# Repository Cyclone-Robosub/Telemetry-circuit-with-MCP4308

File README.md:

# Telemetry-circuit-with-MCP4308
This is the telemetry circuit that Marco Chen made during winter and spring quarter.

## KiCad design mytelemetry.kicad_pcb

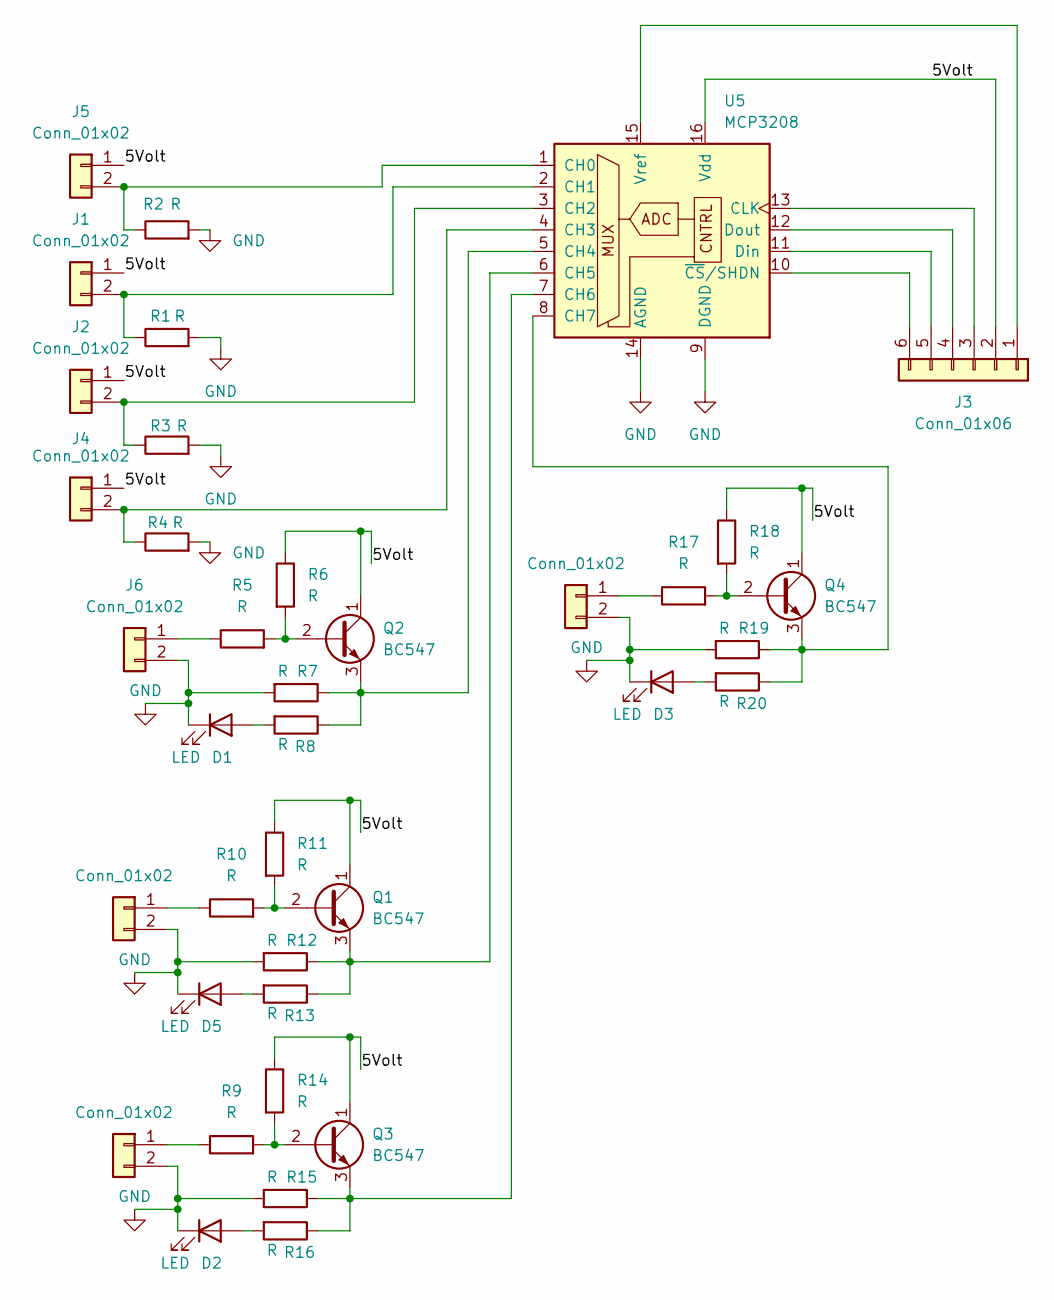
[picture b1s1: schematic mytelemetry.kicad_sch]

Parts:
D1, D2, D3, D5: LED; LED_APT2012LZGCK
J1, J2, J4, J5, J6, J7, J8, J9: Conn_01x02; JST_PH_B2B-PH-K_1x02_P2.00mm_Vertical
J3: Conn_01x06; JST_PH_B6B-PH-K_1x06_P2.00mm_Vertical
Q1, Q2, Q3, Q4: BC547; TO-92_Inline
R1, R2, R3, R4, R5, R6, R7, R8, R9, R10, R11, R12, R13, R14, R15, R16, R17, R18, R19, R20: R; R_0805_2012Metric_Pad1.20x1.40mm_HandSolder
U5: MCP3208; DIP-18_W7.62mm_SMDSocket_SmallPads

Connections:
/5Volt: J1.1, J2.1, J3.2, J4.1, J5.1, Q1.1 (C), Q2.1 (C), Q3.1 (C), Q4.1 (C), R6.1, R11.1, R14.1, R18.1, U5.16 (Vdd); also elsewhere on the board
GND: D1.1 (K), D2.1 (K), D3.1 (K), D5.1 (K), J6.2, J7.2, J8.2, J9.2, R1.2, R2.2, R3.2, R4.2, R7.2, R12.2, R15.2, R19.2, U5.9 (DGND), U5.14 (AGND); also elsewhere on the board
unnamed: D1.2 (A), R8.2
unnamed: D2.2 (A), R16.2
unnamed: D3.2 (A), R20.2
unnamed: D5.2 (A), R13.2
unnamed 6: J1.2, R1.1, U5.2 (CH1); also elsewhere on the board
unnamed 7: J2.2, R3.1, U5.3 (CH2); also elsewhere on the board
unnamed 8: J3.1, U5.15 (Vref); also elsewhere on the board
unnamed 9: J3.3, U5.13 (CLK); also elsewhere on the board
unnamed 10: J3.4, U5.12 (Dout); also elsewhere on the board
unnamed 11: J3.5, U5.11 (Din); also elsewhere on the board
unnamed 12: J3.6, U5.10 (~CS/SHDN); also elsewhere on the board
unnamed 13: J4.2, R4.1, U5.4 (CH3); also elsewhere on the board
unnamed 14: J5.2, R2.1, U5.1 (CH0); also elsewhere on the board
unnamed: J6.1, R5.1
unnamed: J7.1, R10.1
unnamed: J8.1, R9.1
unnamed: J9.1, R17.1
unnamed: Q1.2 (B), R10.2, R11.2
unnamed 20: Q1.3 (E), R12.1, R13.1, U5.6 (CH5); also elsewhere on the board
unnamed: Q2.2 (B), R5.2, R6.2
unnamed 22: Q2.3 (E), R7.1, R8.1, U5.5 (CH4); also elsewhere on the board
unnamed: Q3.2 (B), R9.2, R14.2
unnamed 24: Q3.3 (E), R15.1, R16.1, U5.7 (CH6); also elsewhere on the board
unnamed: Q4.2 (B), R17.2, R18.2
unnamed 26: Q4.3 (E), R19.1, R20.1, U5.8 (CH7); also elsewhere on the board

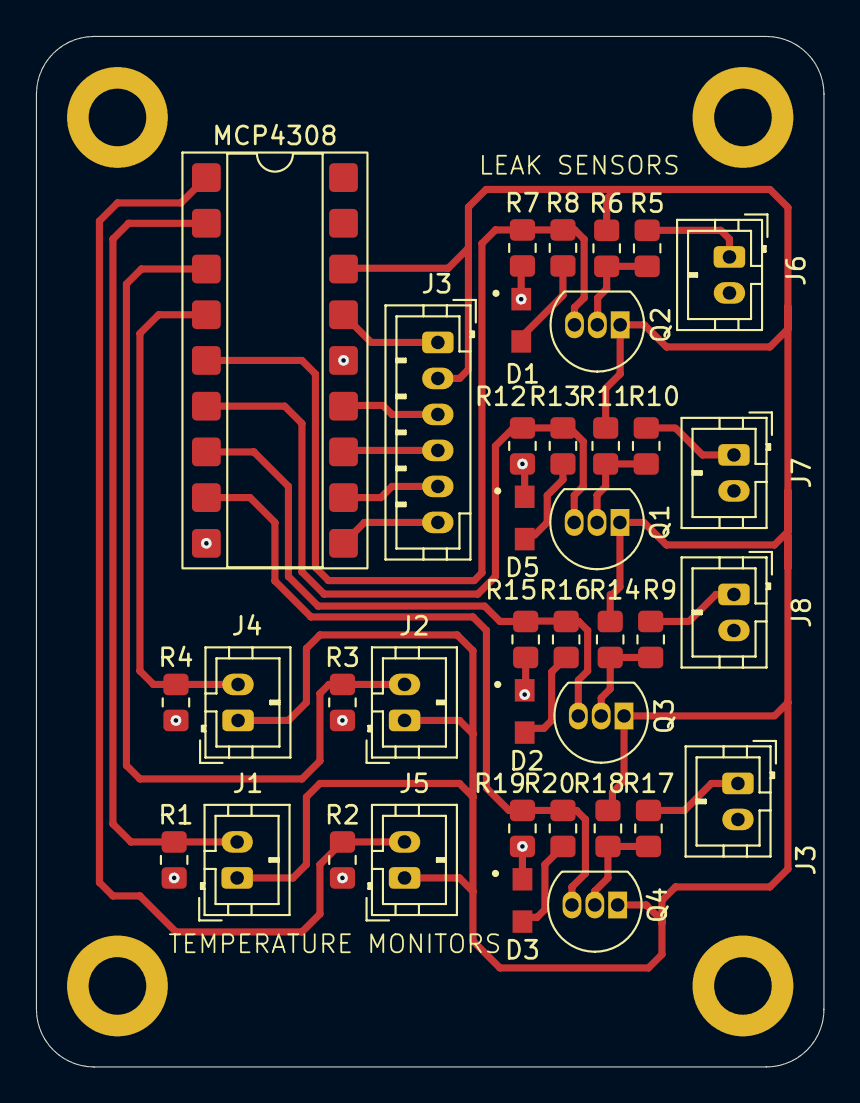
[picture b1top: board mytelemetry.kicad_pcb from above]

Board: 2 copper layers, 43.8 x 57.2 mm, 38 parts (0 on the bottom side), 27 nets.

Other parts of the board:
MCP4308: MCP3208; DIP-18_W7.62mm_SMDSocket_SmallPads

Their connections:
/5Volt: MCP4308.16 (Vdd); also elsewhere on the board
GND: MCP4308.9 (DGND), MCP4308.14 (AGND); also elsewhere on the board
unnamed 6: MCP4308.2 (CH1); also elsewhere on the board
unnamed 7: MCP4308.3 (CH2); also elsewhere on the board
unnamed 8: MCP4308.15 (Vref); also elsewhere on the board
unnamed 9: MCP4308.13 (CLK); also elsewhere on the board
unnamed 10: MCP4308.12 (Dout); also elsewhere on the board
unnamed 11: MCP4308.11 (Din); also elsewhere on the board
unnamed 12: MCP4308.10 (~CS/SHDN); also elsewhere on the board
unnamed 13: MCP4308.4 (CH3); also elsewhere on the board
unnamed 14: MCP4308.1 (CH0); also elsewhere on the board
unnamed 20: MCP4308.6 (CH5); also elsewhere on the board
unnamed 22: MCP4308.5 (CH4); also elsewhere on the board
unnamed 24: MCP4308.7 (CH6); also elsewhere on the board
unnamed 26: MCP4308.8 (CH7); also elsewhere on the board

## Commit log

2026-04-25 This is the first upload of this github
